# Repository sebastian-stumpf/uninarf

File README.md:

# uninarf

[More pictures here](https://imgur.com/a/TW84yVa)

## Attention

I'm a hobbyist/amateur at best. So there may be things that aren't optimized. For example
this board doesn't have a ground plane and some edges aren't rounded properly. That being said I've had the files
in the `gerbers/` directory manufactured at JLC with 1.6mm size and they work just fine with the code provided in the
at https://github.com/sebastian-stumpf/zmk-config-uninarf - So if you decide to use this, then please be advised that
I'm not providing any sort of liability and you should exercise some caution.

## BOM

| Quantity  | Item                               | Comment                                                                            |
| --------- | ---------------------------------- | ---------------------------------------------------------------------------------- |
| 1         | Seeed XIAO BLE                     |                                                                                    |
| 1         | 74HC595 SO-16 Shift Register       | I used 74HC 595D NXP                                                               |
| 42        | 1N4148 SOD123 diodes               |                                                                                    |
| 36        | Choc Hotswap Sockets               |                                                                                    |
| 6         | Omrom 6mm Tact switches            | B3F-1002                                                                           |
| 36        | Choc Switches + Keycaps            |                                                                                    |
| 8         | M2 Screws and Spacers              |                                                                                    |
| 1         | MSK12C02 power switch              |                                                                                    |
| 1         | 1 S2B-PH-K-S(LF)(SN) jack          |                                                                                    |
| 1         | 3.7v lipo battery                  | any size will do as long as it fits between the spacers. I've used a 500mAh 403040 |

## Feedback

I'm always happy to hear your opinions about this and if you decide to build this board then please do send me a picture of it.

## Thanks

Big thanks to [GEIST](https://github.com/GEIGEIGEIST) and his [TOTEM](https://github.com/GEIGEIGEIST/TOTEM) where I grabbed the 
xiao ble footprint from. It makes soldering the MCU a lot easier!

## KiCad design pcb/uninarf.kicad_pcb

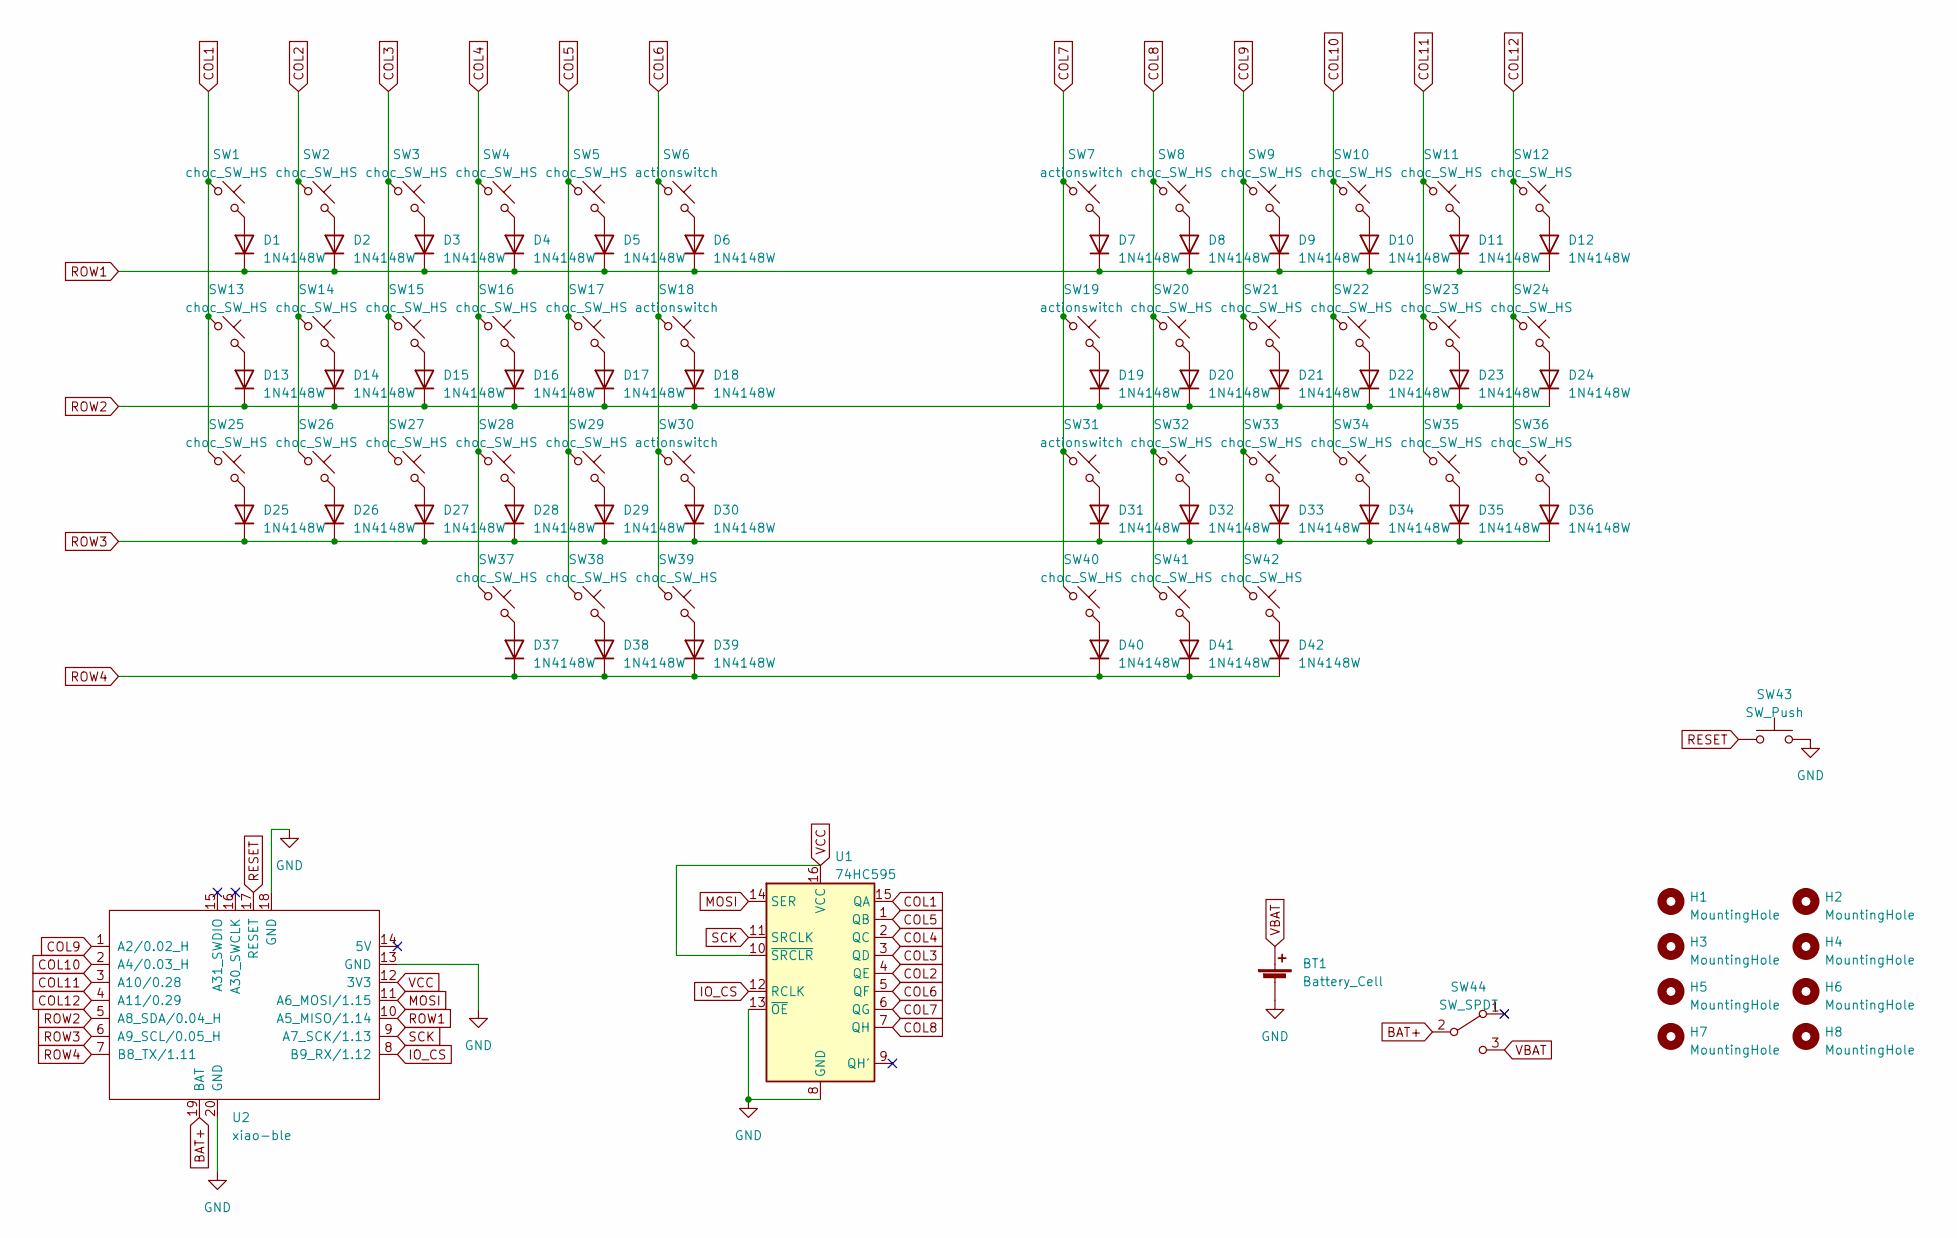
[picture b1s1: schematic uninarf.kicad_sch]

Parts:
BT1: Battery_Cell; JST_PH_S2B-PH-K_1x02_P2.00mm_Horizontal
D1, D2, D3, D4, D5, D6, D7, D8, D9, D10, D11, D12, D13, D14, D15, D16, D17, D18, D19, D20, D21, D22, D23, D24, D25, D26, D27, D28, D29, D30, D31, D32, D33, D34, D35, D36, D37, D38, D39, D40, D41, D42: 1N4148W; D_SOD-123
H1, H2, H3, H4, H5, H6, H7, H8: MountingHole; MountingHole_2.2mm_M2_DIN965
SW1, SW2, SW3, SW4, SW5, SW8, SW9, SW10, SW11, SW12, SW13, SW14, SW15, SW16, SW17, SW20, SW21, SW22, SW23, SW24, SW25, SW26, SW27, SW28, SW29, SW32, SW33, SW34, SW35, SW36, SW37, SW38, SW39, SW40, SW41, SW42: choc_SW_HS; SW_choc_HS_1u
SW6, SW7, SW18, SW19, SW30, SW31: actionswitch
SW43: SW_Push; ResetSW
SW44: SW_SPDT; switch-MSK-12C02-smd
U1: 74HC595; SOP-16_3.9x9.9mm_P1.27mm
U2: xiao-ble; xiao-ble-smd-cutout-geist

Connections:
BAT+: SW44.2 (B), U2.19 (BAT)
COL1: SW1.1, SW13.1, SW25.1, U1.15 (QA)
COL2: SW2.1, SW14.1, SW26.1, U1.4 (QE)
COL3: SW3.1, SW15.1, SW27.1, U1.3 (QD)
COL4: SW4.1, SW16.1, SW28.1, SW37.1, U1.2 (QC)
COL5: SW5.1, SW17.1, SW29.1, SW38.1, U1.1 (QB)
COL6: SW6.1, SW18.1, SW30.1, SW39.1, U1.5 (QF)
COL7: SW7.1, SW19.1, SW31.1, SW40.1, U1.6 (QG)
COL8: SW8.1, SW20.1, SW32.1, SW41.1, U1.7 (QH)
COL9: SW9.1, SW21.1, SW33.1, SW42.1, U2.1 (A2/0.02_H)
COL10: SW10.1, SW22.1, SW34.1, U2.2 (A4/0.03_H)
COL11: SW11.1, SW23.1, SW35.1, U2.3 (A10/0.28)
COL12: SW12.1, SW24.1, SW36.1, U2.4 (A11/0.29)
GND: BT1.2 (-), SW43.2, U1.8 (GND), U1.13 (~OE), U2.13 (GND), U2.18 (GND), U2.20 (GND)
IO_CS: U1.12 (RCLK), U2.8 (B9_RX/1.12)
MOSI: U1.14 (SER), U2.11 (A6_MOSI/1.15)
unnamed: D1.2 (A), SW1.2
unnamed: D2.2 (A), SW2.2
unnamed: D3.2 (A), SW3.2
unnamed: D4.2 (A), SW4.2
unnamed: D5.2 (A), SW5.2
unnamed: D6.2 (A), SW6.2
unnamed: D7.2 (A), SW7.2
unnamed: D8.2 (A), SW8.2
unnamed: D9.2 (A), SW9.2
unnamed: D10.2 (A), SW10.2
unnamed: D11.2 (A), SW11.2
unnamed: D12.2 (A), SW12.2
unnamed: D13.2 (A), SW13.2
unnamed: D14.2 (A), SW14.2
unnamed: D15.2 (A), SW15.2
unnamed: D16.2 (A), SW16.2
unnamed: D17.2 (A), SW17.2
unnamed: D18.2 (A), SW18.2
unnamed: D19.2 (A), SW19.2
unnamed: D20.2 (A), SW20.2
unnamed: D21.2 (A), SW21.2
unnamed: D22.2 (A), SW22.2
unnamed: D23.2 (A), SW23.2
unnamed: D24.2 (A), SW24.2
unnamed: D25.2 (A), SW25.2
unnamed: D26.2 (A), SW26.2
unnamed: D27.2 (A), SW27.2
unnamed: D28.2 (A), SW28.2
unnamed: D29.2 (A), SW29.2
unnamed: D30.2 (A), SW30.2
unnamed: D31.2 (A), SW31.2
unnamed: D32.2 (A), SW32.2
unnamed: D33.2 (A), SW33.2
unnamed: D34.2 (A), SW34.2
unnamed: D35.2 (A), SW35.2
unnamed: D36.2 (A), SW36.2
unnamed: D37.2 (A), SW37.2
unnamed: D38.2 (A), SW38.2
unnamed: D39.2 (A), SW39.2
unnamed: D40.2 (A), SW40.2
unnamed: D41.2 (A), SW41.2
unnamed: D42.2 (A), SW42.2
RESET: SW43.1, U2.17 (RESET)
ROW1: D1.1 (K), D2.1 (K), D3.1 (K), D4.1 (K), D5.1 (K), D6.1 (K), D7.1 (K), D8.1 (K), D9.1 (K), D10.1 (K), D11.1 (K), D12.1 (K), U2.10 (A5_MISO/1.14)
ROW2: D13.1 (K), D14.1 (K), D15.1 (K), D16.1 (K), D17.1 (K), D18.1 (K), D19.1 (K), D20.1 (K), D21.1 (K), D22.1 (K), D23.1 (K), D24.1 (K), U2.5 (A8_SDA/0.04_H)
ROW3: D25.1 (K), D26.1 (K), D27.1 (K), D28.1 (K), D29.1 (K), D30.1 (K), D31.1 (K), D32.1 (K), D33.1 (K), D34.1 (K), D35.1 (K), D36.1 (K), U2.6 (A9_SCL/0.05_H)
ROW4: D37.1 (K), D38.1 (K), D39.1 (K), D40.1 (K), D41.1 (K), D42.1 (K), U2.7 (B8_TX/1.11)
SCK: U1.11 (SRCLK), U2.9 (A7_SCK/1.13)
VBAT: BT1.1 (+), SW44.3 (C)
VCC: U1.10 (~SRCLR), U1.16 (VCC), U2.12 (3V3)

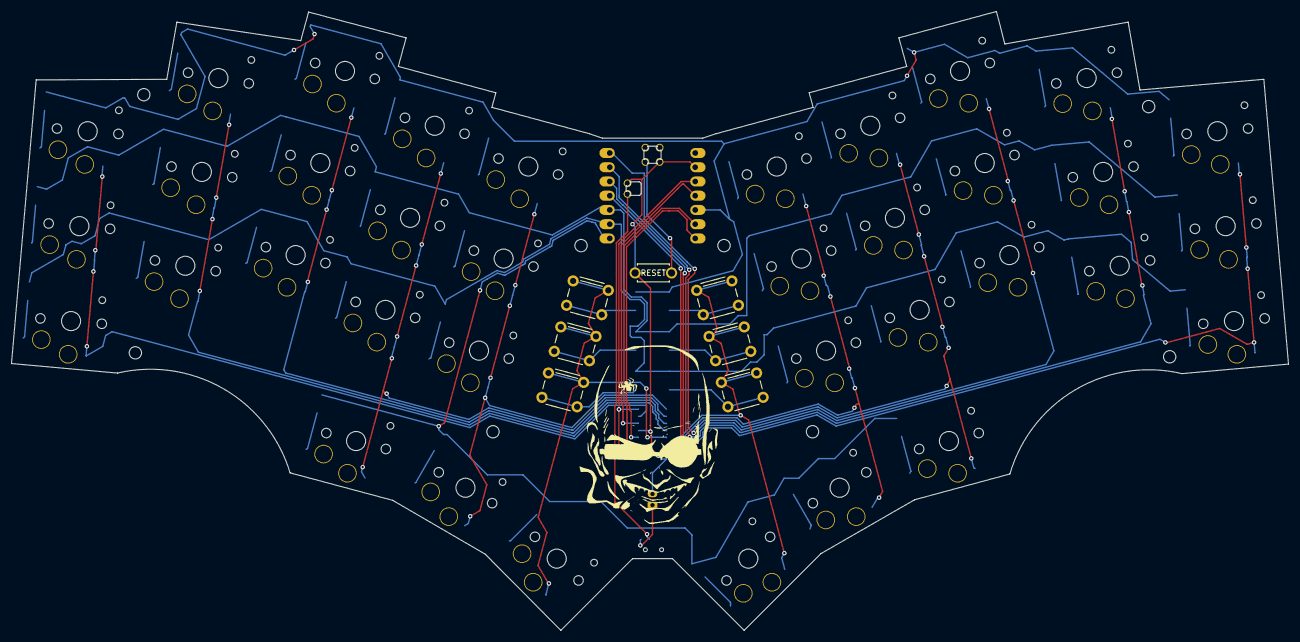
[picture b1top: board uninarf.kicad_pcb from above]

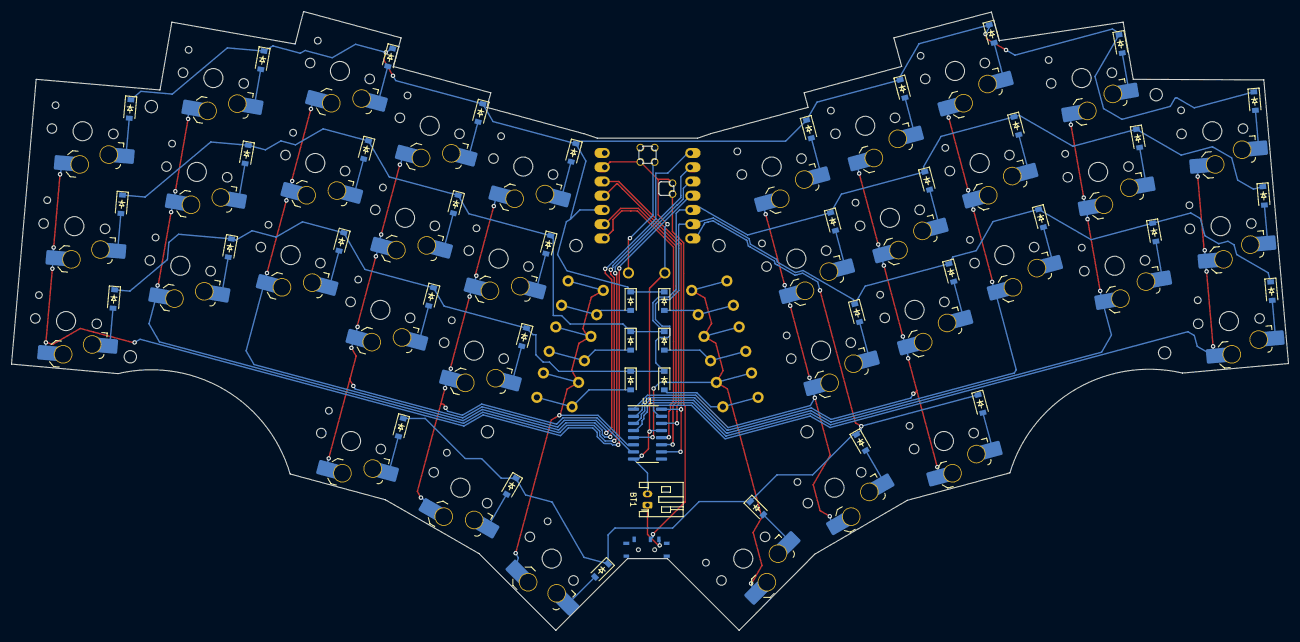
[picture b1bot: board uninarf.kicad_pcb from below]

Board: 2 copper layers, 227.8 x 110.4 mm, 97 parts (45 on the bottom side), 66 nets.

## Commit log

2023-04-29 expanded bom
2023-05-08 Create LICENSE
2023-05-10 added case
